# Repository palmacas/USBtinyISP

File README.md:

# USBtinyISP

The USBtinyISP is an USB ISP programmer for Atmel AVRs.

---
More information:  
[Programador USBtinyISP](https://palmacas.com/usbtinyisp-programmer/)  [[Spanish]](https://palmacas.com/programador-usbtinyisp/)  
[USBtiny Project](https://dicks.home.xs4all.nl/avr/usbtiny/)  
[AVR programmer &amp; SPI interface](https://learn.adafruit.com/usbtinyisp)

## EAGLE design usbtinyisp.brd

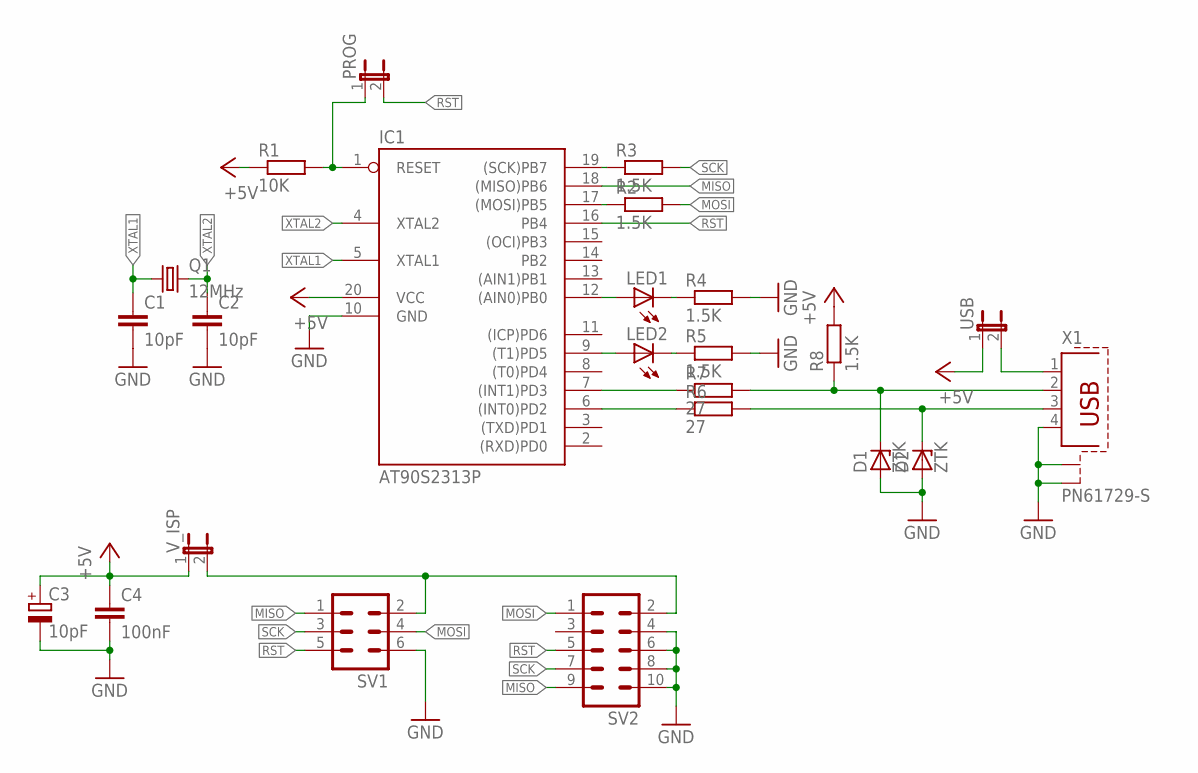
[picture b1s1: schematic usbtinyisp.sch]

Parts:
C1, C2: 10pF; C025-025X050
C3: 10pF; E2,5-6E
C4: 100nF; C025-025X050
D1, D2: ZTK; DO35Z10
IC1: AT90S2313P; DIL20
LED1, LED2: LED3MM
PROG: JP1E; JP1
Q1: 12MHz; HC49U70
R1: 10K; 0207/7
R2, R3, R4, R5, R8: 1.5K; 0207/7
R6, R7: 27; 0207/7
SV1: MA03-2
SV2: MA05-2
USB: JP1E; JP1
V_ISP: JP1E; JP1
X1: PN61729-S

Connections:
+5V: C3.+, C4.1, IC1.20 (VCC), R1.1, R8.2, USB.1, V_ISP.1
GND: C1.2, C2.2, C3.-, C4.2, D1.A, D2.A, IC1.10 (GND), R4.2, R5.2, SV1.6, SV2.4, SV2.6, SV2.8, SV2.10, X1.4, X1.S1, X1.S2
MISO: IC1.18 ((MISO)PB6), SV1.1, SV2.9
MOSI: R2.2, SV1.4, SV2.1
unnamed: IC1.1 (RESET), PROG.1, R1.2
unnamed: IC1.12 ((AIN0)PB0), LED1.A
unnamed: IC1.9 ((T1)PD5), LED2.A
unnamed: LED1.K (C), R4.1
unnamed: LED2.K (C), R5.1
unnamed: IC1.7 ((INT1)PD3), R7.1
unnamed: IC1.17 ((MOSI)PB5), R2.1
unnamed: IC1.19 ((SCK)PB7), R3.1
unnamed: IC1.6 ((INT0)PD2), R6.1
unnamed: D2.C, R6.2, X1.3
unnamed: D1.C, R7.2, R8.1, X1.2
unnamed: USB.2, X1.1
unnamed: SV1.2, SV2.2, V_ISP.2
RST: IC1.16 (PB4), PROG.2, SV1.5, SV2.5
SCK: R3.2, SV1.3, SV2.7
XTAL1: C1.1, IC1.5 (XTAL1), Q1.1
XTAL2: C2.1, IC1.4 (XTAL2), Q1.2

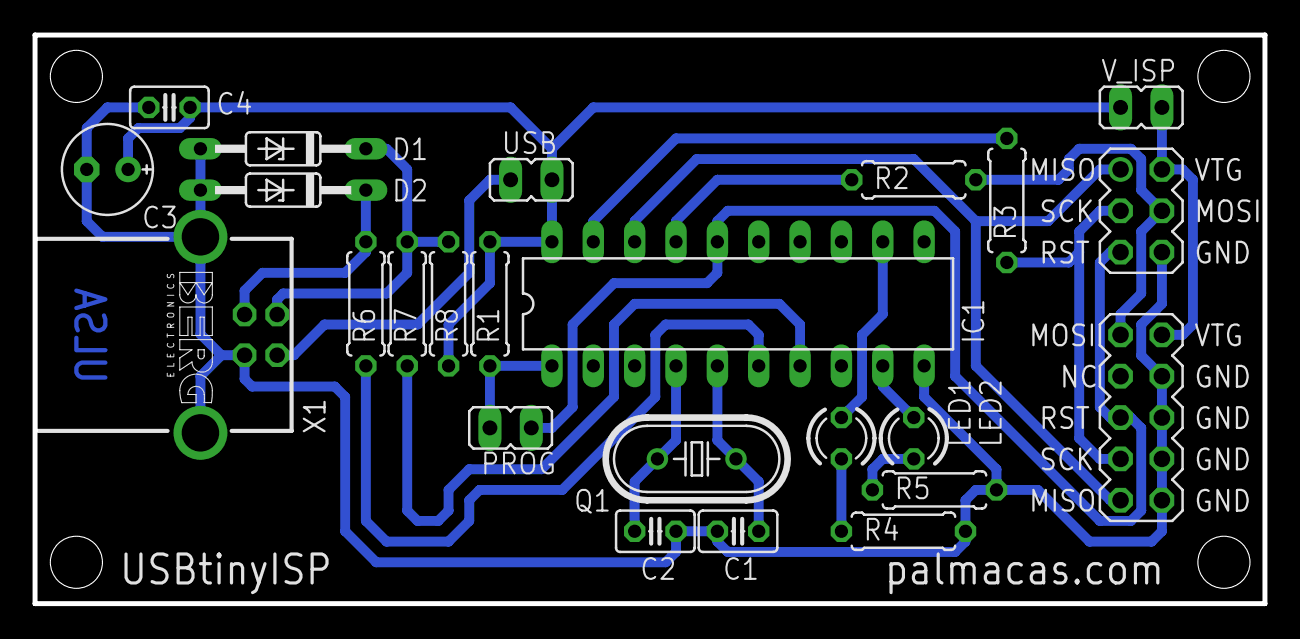
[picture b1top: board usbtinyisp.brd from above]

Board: 2 copper layers, 75.5 x 34.9 mm, 24 parts (0 on the bottom side), 21 nets.

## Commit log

2020-06-02 Update LICENSE
